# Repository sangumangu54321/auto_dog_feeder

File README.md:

# DEMO
https://github.com/user-attachments/assets/b3031224-225a-4a62-bf17-dde1cf52a47b

# hacktime

# what is that?
This is a device which feed the dog automaticly or just with a one click with a help of mobile application

# feature 
- Wifi connectivite (use it from any conear of the world)
- Modile application (user friendly expreance)
- Scheduling even work offline (ensure the user of dog health) 
- really time food status bar (help the user to know does there dog eat the food)
- have a load cell (help the machine to give proper amount of food)
- backup battery (To ensure the device must be online 24/7 )

# PCB
## Schematic 

## board

## 3D model

# Model

## CAD

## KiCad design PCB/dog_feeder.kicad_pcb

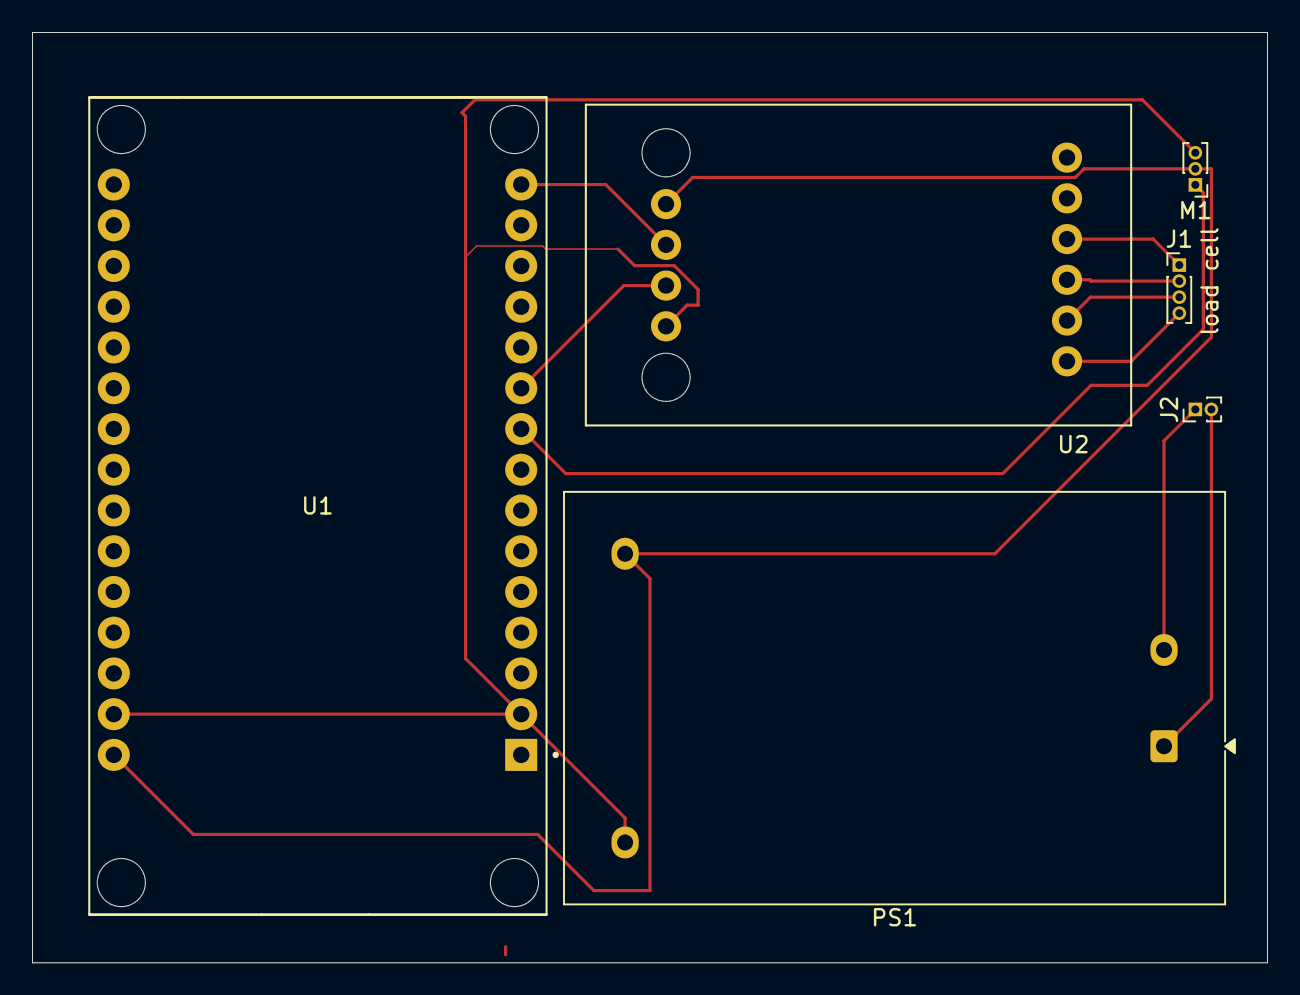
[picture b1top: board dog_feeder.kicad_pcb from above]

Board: 2 copper layers, 77.0 x 58.0 mm, 6 parts (0 on the bottom side), 11 nets.

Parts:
J1: Conn_01x04_MountingPin; PinHeader_1x04_P1.00mm_Vertical
J2: 240V; PinHeader_1x02_P1.00mm_Vertical
M1: Servo; PinHeader_1x03_P1.00mm_Vertical
PS1: HLK-5M05; Converter_ACDC_Hi-Link_HLK-5Mxx
U1: ESP32-DEVKIT-V1; MODULE_ESP32_DEVKIT_V1
U2: HX711-Mod; HX711_module

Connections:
+5V: M1.2 (+), PS1.4 (+Vout), U1.30 (VIN), U2.7 (VDD)
GND: M1.3 (-), PS1.3 (-Vout), U1.2 (GND), U2.10 (GND)
LINE: J2.2, PS1.1 (AC/L)
NEUT: J2.1, PS1.2 (AC/N)
unnamed: J1.1, U2.4 (A+_(V))
unnamed: J1.2, U2.3 (A-_(B))
unnamed: J1.3, U2.2 (E-_(N))
unnamed: J1.4, U2.1 (E+_(R))
unnamed: M1.1 (PWM), U1.9 (D18)
unnamed: U1.10 (D19), U2.9 (DAT)
unnamed: U1.15 (D23), U2.8 (CLK)

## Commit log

2026-01-07 PCB ADDED
2026-01-07 Create DEMO
